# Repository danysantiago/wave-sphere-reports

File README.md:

wave-sphere-reports
===================

Latex reports for the class ICOM5217 - Microprocessor Interfacing and the WaveSphere project.

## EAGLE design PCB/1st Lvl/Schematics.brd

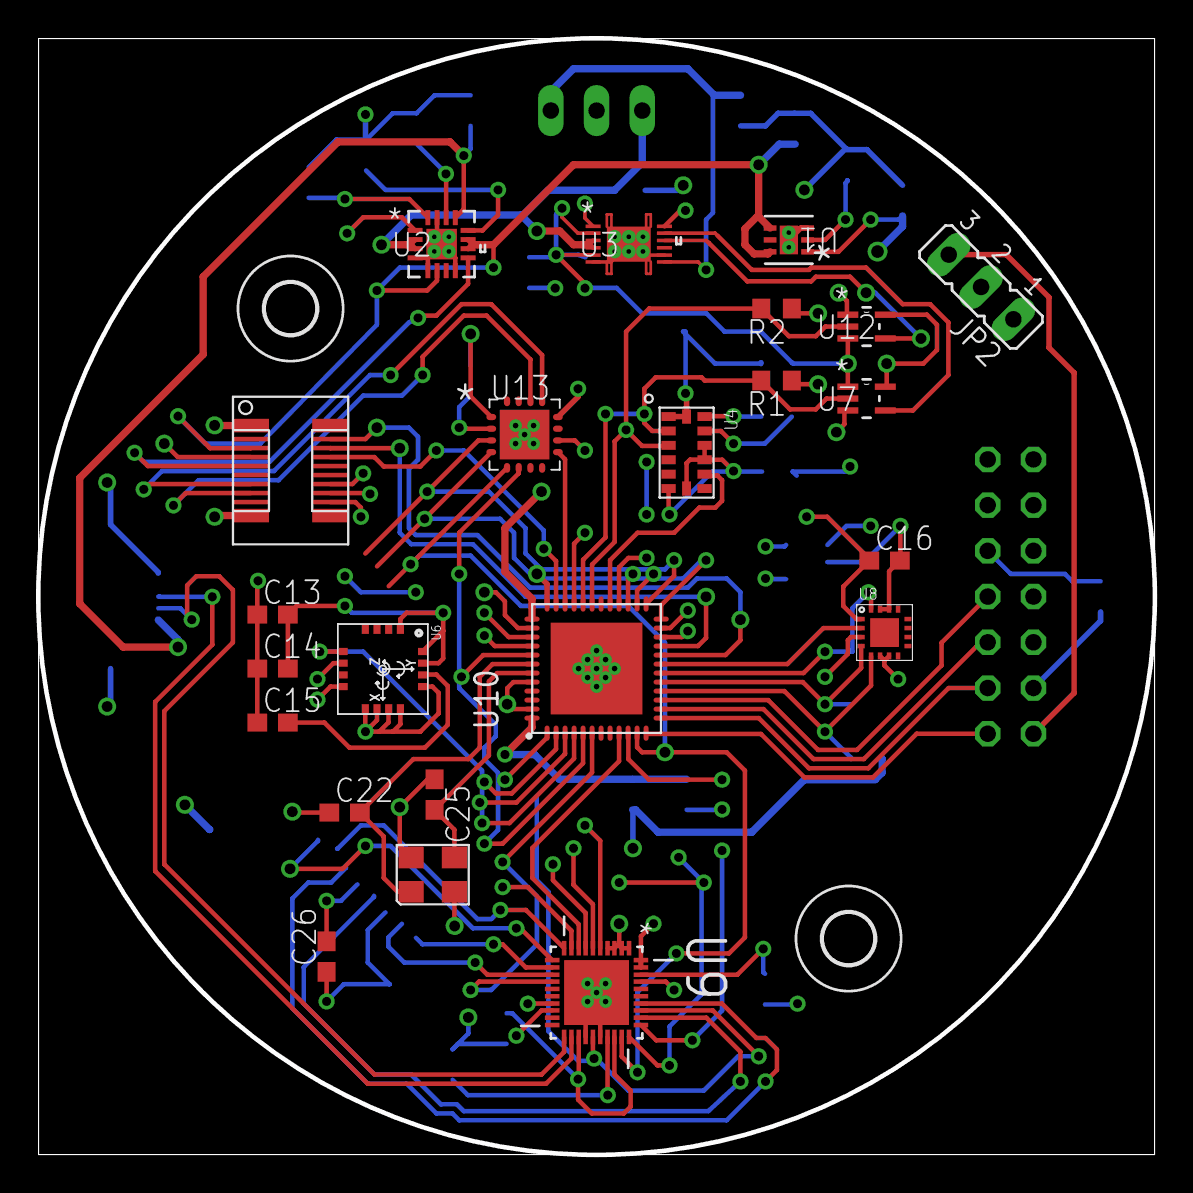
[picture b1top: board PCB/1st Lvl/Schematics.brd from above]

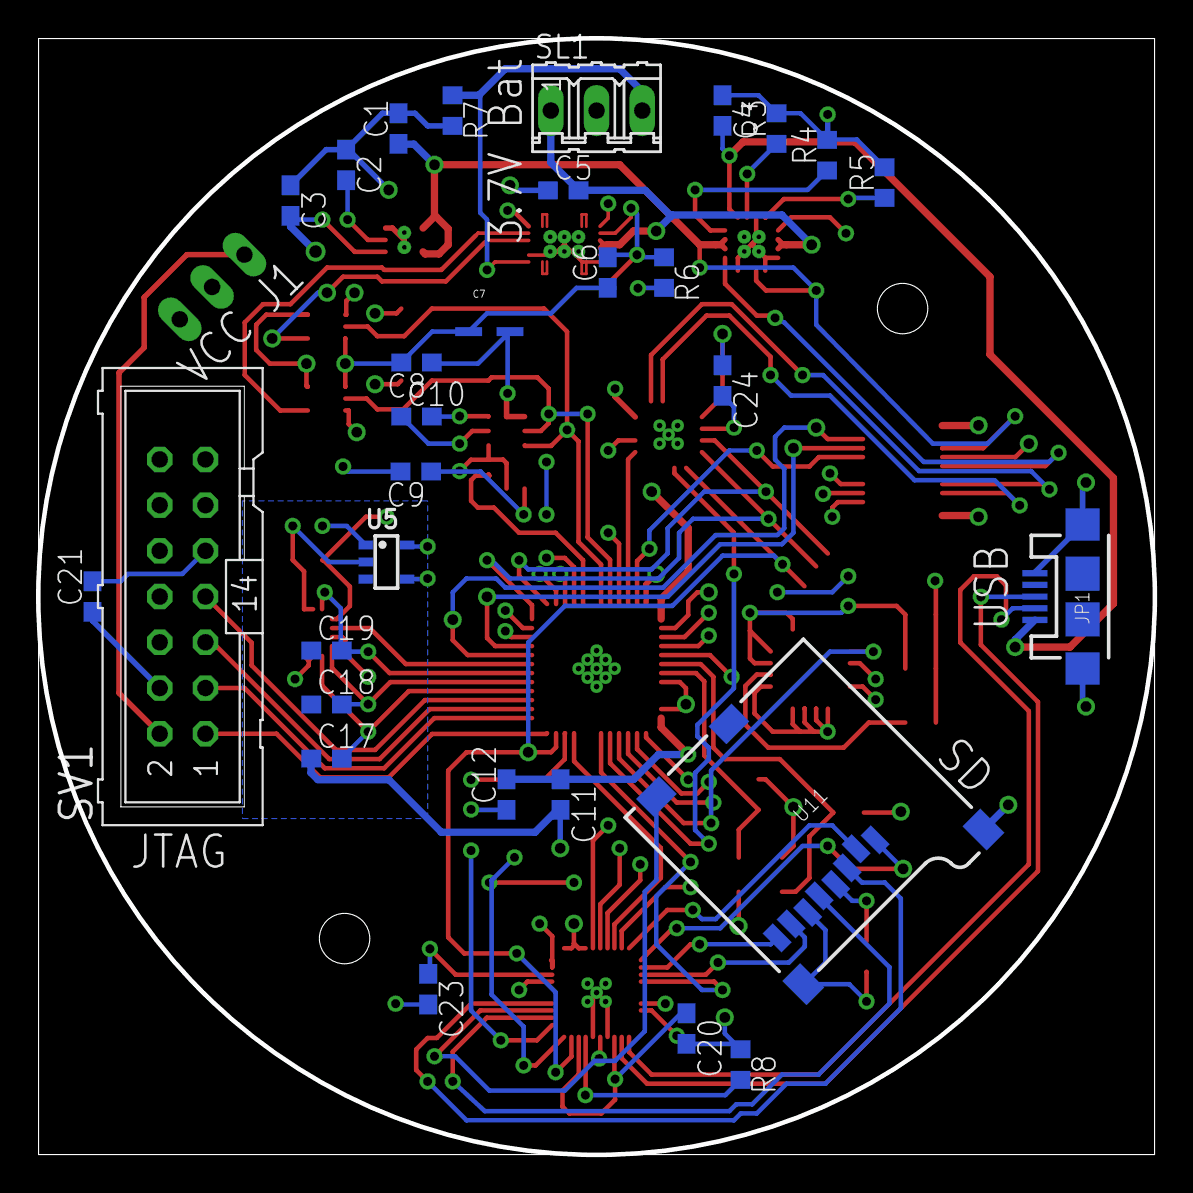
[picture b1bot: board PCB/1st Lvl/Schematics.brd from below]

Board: 4 copper layers, 62.0 x 62.0 mm, 55 parts (30 on the bottom side), 72 nets.

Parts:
C1, C5, C9: 4.7u; C0603
C2, C17, C18, C19: 0.01u; C0603
C3: 2.2u; C0603
C4, C11, C12, C20, C23, C26: 1u; C0603
C6, C8, C13, C14, C16, C24: 0.1u; C0603
C7: 10u; ELECTROLYTIC_CAP
C10: 0.22u; C0603
C15: 1n; C0603
C21: 2.2n; C0603
C22, C25: 22p; C0603
JP1: USB-MICROB
JP2: JP2
JP3: 20-SOCKET
R1, R2: 10k; R0603
R3: 18.7k; R0603
R4: 1.5k; R0603
R5: 1.8k; R0603
R6: 1.8M; R0603
R7: 10m; R0603
R8: 6.19k; R0603
SL1: 3.7V; 03P
SV1: ML14
U1: TPS73533; DRV6_1P6X1
U2: BQ24072_RGT_16; RGT16_1P7X1P7
U3: BQ27410-G1_DRZ_12; DRZ12_1P95X2P45
U4: LSM303DLHC; LGA_3X5X1_14L
U5: BU4S66G2; SSOP5
U6: L3GD20
U7, U12: SN74CB3T1G125_DCK_5; DCK5
U8: ADXL377; LFCSP-16
U9: MAX14502AETL+; QFN40P500X500X80-41N
U10: MSP430FR5969V2; RGZ(S-PVQFN-N48)
U11: SPARKFUN_USD-SOCKETSMD; SPARKFUN_MICRO-SD-SOCKET-PP
U13: AS3930
U$2, U$4: 2,8
X1: 12MHZ

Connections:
AGND: C11.2, C16.1, C17.1, C18.1, C19.1, U5.3, U8.1, U8.3, U8.6, U8.7, U10.41, U10.44, U10.47
BAT_SOC: U3.12, U10.10
CHRG_VCC: C1.1, JP3.3, U1.4, U1.6, U2.6, U2.10, U2.11
D+: JP1.D+, U9.22
D-: JP1.D-, U9.21
GND: C1.2, C2.1, C3.1, C4.1, C5.1, C6.1, C7.-, C8.2, C9.2, C12.1, C13.1, C14.1, C15.1, C20.2, C21.2, C22.1, C23.2, C24.1, C25.1, C26.1, JP1.GND, JP1.MT1, JP1.MT2, JP3.10, R3.2, R4.2, R5.2, R7.2, R8.1, SV1.9, U1.3, U1.7, U1.V, U1.V_2, U2.4, U2.5, U2.8, U2.15, U2.17, U2.V, U2.V_2, U2.V_3, U2.V_4, U3.6, U3.8, U3.13, U3.V, U3.V_2, U3.V_3, U3.V_4, U3.V_5, U3.V_6, U4.P7, U4.P10, U4.P11, U6.4, U6.8, U6.9, U6.10, U6.11, U6.12, U6.13, U7.1, U7.3, U9.1, U9.2, U9.3, U9.4, U9.18, U9.24, U9.26, U9.37, U9.41, U10.36, U10.VSS_QFN, U11.6, U11.GND1, U11.GND2, U12.1, U12.3, U13.7, U13.16, U13.EXP, X1.P$2, X1.P$4
GPS_FIX: JP3.12, U10.3
GYR_DR: U6.6, U10.28
I2CCLK: R1.2, U4.P2, U6.2, U7.2, U10.32
I2CDAT: R2.2, U4.P3, U6.3, U10.31, U12.2
LED1: JP3.5, U2.9
MAG_DR: U4.P9, U10.29
MCU_LED: JP3.4, U10.38
unnamed: U5.5, U10.33
unnamed: C16.2, U5.2, U8.14, U8.15
unnamed: SL1.2, U2.1
unnamed: U3.11, U7.4
unnamed: U8.2, U10.19
unnamed: U3.10, U12.4
unnamed: C15.2, U6.14
unnamed: SV1.1, U10.12
unnamed: C11.1, C12.2, JP2.2, U10.37, U10.48
unnamed: SV1.3, U10.13
unnamed: C22.2, U10.42, X1.P$1
unnamed: C25.2, U10.43, X1.P$3
unnamed: U9.10, U11.2
unnamed: U9.11, U11.1
unnamed: C17.2, U8.5, U10.16
unnamed: U9.12, U11.8
unnamed: C18.2, U8.4, U10.17
unnamed: C19.2, U8.16, U10.18
unnamed: R6.2, U3.1
unnamed: U9.13, U11.7
unnamed: C9.1, U4.P6
unnamed: C10.1, U4.P12
unnamed: C10.2, U4.P13
unnamed: R5.1, U2.16
unnamed: R4.1, U2.12
unnamed: R3.1, U2.14
unnamed: C2.2, U1.2
unnamed: U9.34, U11.3
unnamed: R7.1, SL1.3, U3.7
unnamed: SV1.5, U10.14
unnamed: U9.32, U11.5
unnamed: SV1.7, U10.15
unnamed: C5.2, SL1.1, U2.2, U2.3, U3.3, U3.4
unnamed: U9.33, U11.CD2
unnamed: SV1.8, U10.22
unnamed: R8.2, U9.27
unnamed: C23.1, U9.38
RFWK_CS: U10.5, U13.11
RF_LFN: JP3.7, U13.4
RF_LFP: JP3.8, U13.3
RF_WK: U10.34, U13.8
SD_CD: U9.30, U10.26
SD_CS: U9.14, U10.6
SPI_CLK: U9.29, U10.11, U13.12
SPI_MISO: U9.17, U10.25, U13.14
SPI_MOSI: U9.31, U10.24, U13.13
SU_BERR: U9.6, U10.40
SU_BUSY: U9.7, U10.39
SU_FREF: U9.25, U10.27
SU_MODE: U9.8, U10.9
SWUARTRX: JP3.13, U10.2
SWUARTTX: JP3.14, U10.1
UARTRX: JP3.18, U10.21
UARTTX: JP3.19, U10.20
V2.5: C6.2, R6.1, U3.2, U3.5, U7.5, U12.5
VBUS: C4.2, JP1.VBUS, U2.13
VCC: C3.2, C7.+, C8.1, C13.2, C14.2, C20.1, C21.1, C24.2, C26.2, JP2.1, JP3.1, R1.1, R2.1, SV1.4, SV1.11, U1.1, U4.P1, U4.P14, U5.1, U5.4, U6.1, U6.5, U6.15, U6.16, U9.5, U9.9, U9.23, U9.28, U9.39, U9.40, U10.23, U11.4, U13.5, U13.15
VCC_JTAG: JP2.3, SV1.2
XB_SLEEP: JP3.17, U10.35

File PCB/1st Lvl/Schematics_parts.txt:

Part	Value	Package	Library	Position	Layer

C1  	4.7u  	C0603  	rcl 	  1654   2244	16
C2  	0.01u  	C0603  	rcl 	  1768   2165	16
C3  	2.2u  	C0603  	rcl 	  1890   2087	16
C4  	1u  	C0603  	rcl 	   945   2283	16
C5  	4.7u  	C0603  	rcl 	  1293   2109	16
C6  	0.1u  	C0603  	rcl 	  1196   1929	16
C7  	10u  	ELECTROLYTIC_CAP  	Micro2 	  1455   1800	16
C8  	0.1u  	C0603  	rcl 	  1614   1732	16
C9  	4.7u  	C0603  	rcl 	  1616   1494	16
C10  	0.22u  	C0603  	rcl 	  1614   1614	16
C11  	1u  	C0603  	rcl 	  1299    787	16
C12  	1u  	C0603  	rcl 	  1417    787	16
C13  	0.1u  	C0603  	rcl 	   512   1181	1
C14  	0.1u  	C0603  	rcl 	   512   1063	1
C15  	1n  	C0603  	rcl 	   512    945	1
C16  	0.1u  	C0603  	rcl 	  1850   1299	1
C17  	0.01u  	C0603  	rcl 	  1811    866	16
C18  	0.01u  	C0603  	rcl 	  1811    984	16
C19  	0.01u  	C0603  	rcl 	  1811   1102	16
C20  	1u  	C0603  	rcl 	  1024    276	16
C21  	2.2n  	C0603  	rcl 	  2323   1220	16
C22  	22p  	C0603  	rcl 	   669    748	1
C23  	1u  	C0603  	rcl 	  1589    362	16
C24  	0.1u  	C0603  	rcl 	   945   1693	16
C25  	22p  	C0603  	rcl 	   866    787	1
C26  	1u  	C0603  	rcl 	   630    433	1
JP1  	USB-MICROB  	USB-MICROB  	SparkFun-Connectors 	   157   1220	16
JP2  	  	JP2  	jumper 	  2061   1898	1
JP3  	20-SOCKET  	20-SOCKET  	Micro2 	   551   1496	1
R1  	1.8k  	R0603  	rcl 	  1614   1693	1
R2  	1.8k  	R0603  	rcl 	  1614   1850	1
R3  	18.7k  	R0603  	rcl 	   827   2244	16
R4  	1.5k  	R0603  	rcl 	   716   2186	16
R6  	1.8k  	R0603  	rcl 	   591   2126	16
R7  	1.8M  	R0603  	rcl 	  1073   1929	16
R12  	10m  	R0603  	rcl 	  1535   2283	16
R15  	6.19k  	R0603  	rcl 	   906    197	16
SL1  	3.7V  	03P  	con-amp-quick 	  1220   2283	16
SV1  	  	ML14  	con-ml 	  2126   1220	16
U$2  	  	2,8  	holes 	   551   1850	1
U$4  	  	2,8  	holes 	  1772    472	1
U1  	TPS73533  	DRV6_1P6X1  	Micro2 	  1641   2001	1
U2  	BQ24072_RGT_16  	RGT16_1P7X1P7  	Micro2 	   881   1991	1
U3  	BQ27410-G1_DRZ_12  	DRZ12_1P95X2P45  	Micro2 	  1291   1991	1
U4  	LSM303DLHC  	LGA_3X5X1_14L  	Micro2 	  1417   1535	1
U5  	BU4S66G2  	SSOP5  	Micro2 	  1680   1296	16
U6  	L3GD20  	L3GD20  	Micro2 	   753   1062	1
U7  	SN74CB3T1G125_DCK_5  	DCK5  	Micro2 	  1811   1654	1
U8  	ADXL377  	LFCSP-16  	Micro2 	  1850   1142	1
U9  	MAX14502AETL+  	QFN40P500X500X80-41N  	Micro2 	  1220    354	1
U10  	MSP430FR5969V2  	RGZ(S-PVQFN-N48)  	Micro2 	  1220   1063	1
U11  	SPARKFUN_USD-SOCKETSMD  	SPARKFUN_MICRO-SD-SOCKET-PP  	Micro2 	  1158    737	16
U12  	SN74CB3T1G125_DCK_5  	DCK5  	Micro2 	  1811   1811	1
U13  	AS3930  	AS3930  	Micro2 	  1063   1575	1
X1  	12MHZ  	12MHZ  	12Mhz 	   787    551	1

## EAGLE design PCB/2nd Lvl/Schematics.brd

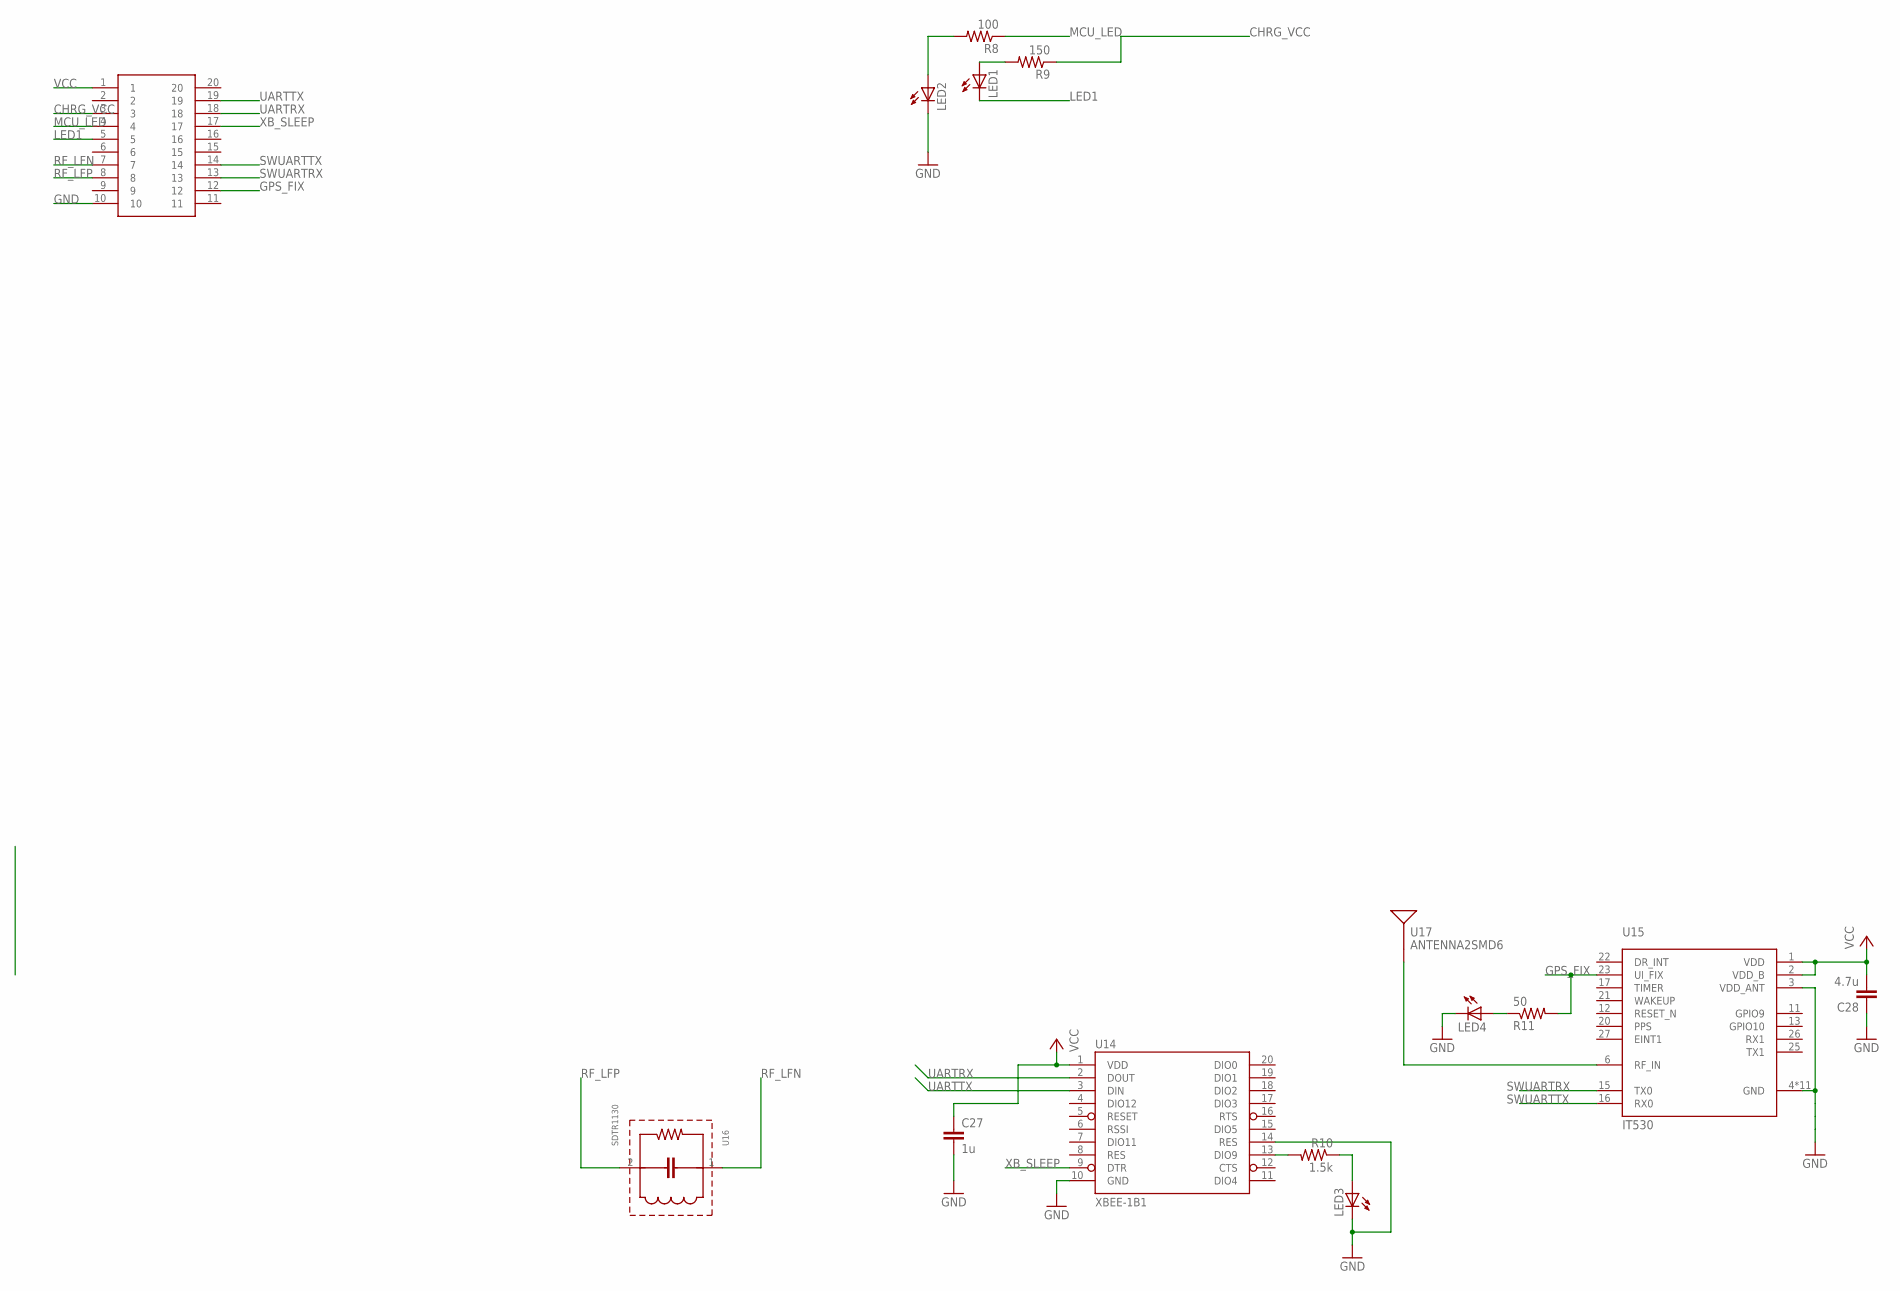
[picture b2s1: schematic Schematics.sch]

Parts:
C27: 1u; C0603
C28: 4.7u; C0603
JP4: 20-HEAD
LED1, LED2, LED3, LED4: LED; SMARTLED-TTW
R8: 100; R0603
R9: 150; R0603
R10: 1.5k; R0603
R11: 50; R0603
U14: XBEE-1B1; XBEE-1
U15: IT530
U16: SDTR1130; SDTR1130-SMD
U17: ANTENNA2SMD6; ANTENNA-CHIP6

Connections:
CHRG_VCC: JP4.3, R9.1
GND: C27.2, C28.1, JP4.10, LED2.C@1 (C), LED3.C@1 (C), LED4.C@1 (C), U14.10 (GND), U14.14 (RES), U15.3 (VDD_ANT), U15.4 (GND), U15.5 (GND), U15.7 (GND), U15.8 (GND), U15.9 (GND), U15.10 (GND), U15.14 (GND), U15.18 (GND), U15.19 (GND), U15.24 (GND), U15.28 (GND)
GPS_FIX: JP4.12, R11.2, U15.23 (UI_FIX)
LED1: JP4.5, LED1.C@1 (C)
MCU_LED: JP4.4, R8.1
unnamed: LED4.A@1 (A), R11.1
unnamed: LED3.A@1 (A), R10.1
unnamed: R10.2, U14.13 (DIO9)
unnamed: U15.6 (RF_IN), U17.1
unnamed: LED1.A@1 (A), R9.2
unnamed: LED2.A@1 (A), R8.2
RF_LFN: JP4.7, U16.1
RF_LFP: JP4.8, U16.2
SWUARTRX: JP4.13, U15.15 (TX0)
SWUARTTX: JP4.14, U15.16 (RX0)
UARTRX: JP4.18, U14.2 (DOUT)
UARTTX: JP4.19, U14.3 (DIN)
VCC: C27.1, C28.2, JP4.1, U14.1 (VDD), U15.1 (VDD), U15.2 (VDD_B)
XB_SLEEP: JP4.17, U14.9 (DTR)

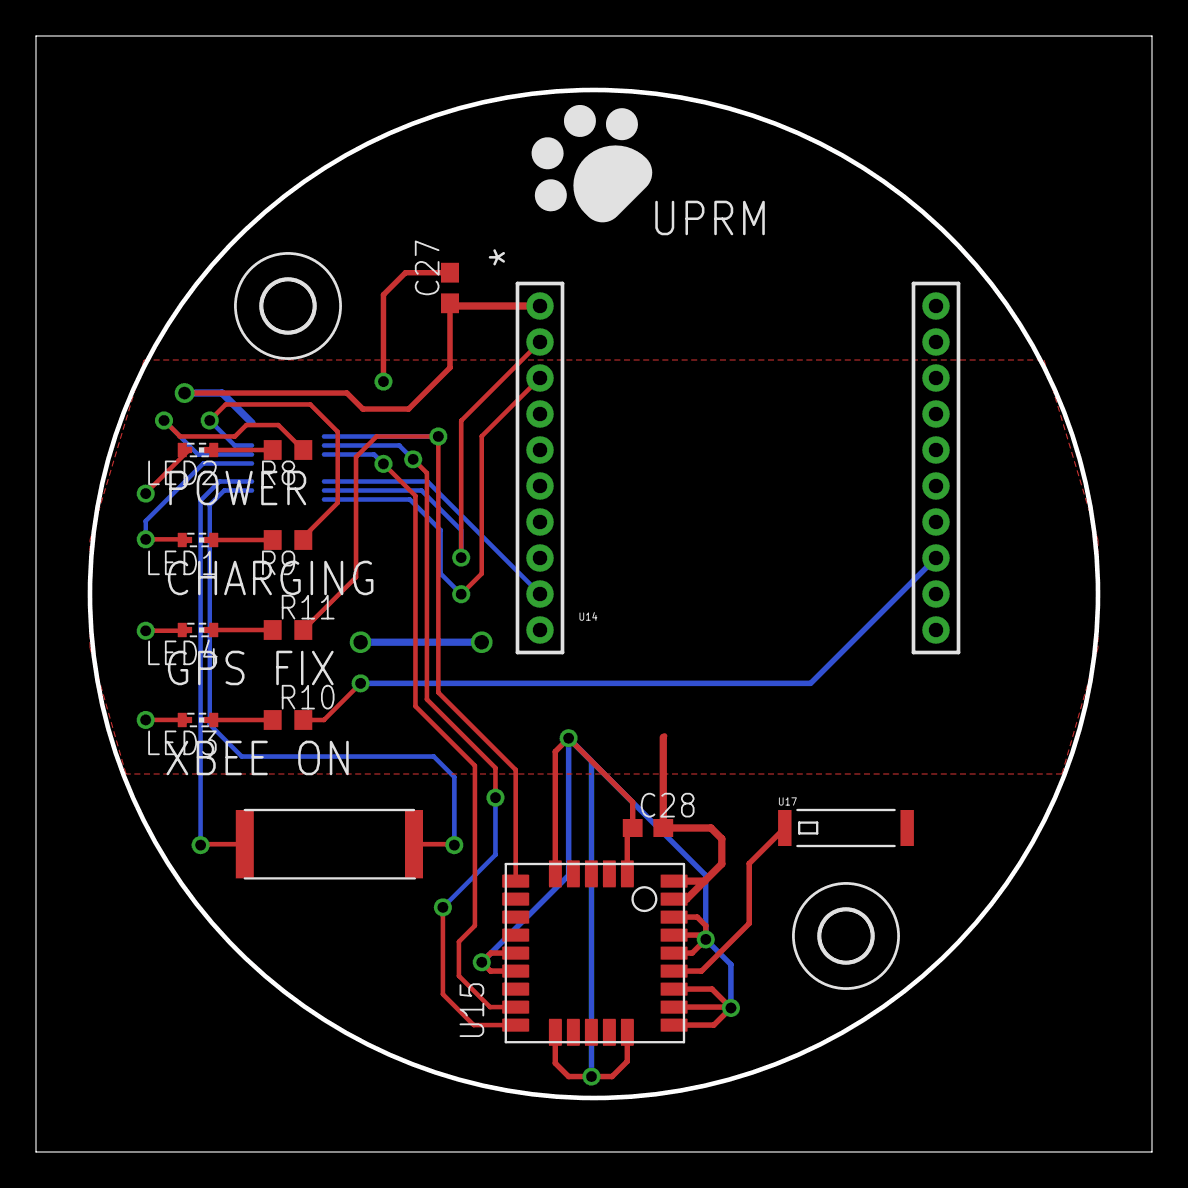
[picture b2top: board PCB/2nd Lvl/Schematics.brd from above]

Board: 2 copper layers, 62.0 x 62.0 mm, 17 parts (1 on the bottom side), 19 nets.

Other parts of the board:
U$4, U$5: 2,8

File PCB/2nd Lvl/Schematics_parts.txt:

EAGLE Version 6.0.0 Copyright (c) 1988-2011 CadSoft
Board partlist for devices with packages for C:/Users/Adrian/Documents/GitHub/wave-sphere-reports/PCB/2nd Lvl/Schematics.sch at 29.04.2013 15:11:53.
The tabulator separated list has been generated with 'Parts v1.3

Part	Value	Package	Library	Position	Layer

C27  	1u  	C0603  	rcl 	   906   1890	1
C28  	4.7u  	C0603  	rcl 	  1339    709	1
JP4  	20-HEAD  	20-HEAD  	Micro2 	   551   1496	16
LED1  	  	SMARTLED-TTW  	led 	   354   1339	1
LED2  	  	SMARTLED-TTW  	led 	   354   1535	1
LED3  	  	SMARTLED-TTW  	led 	   354    945	1
LED4  	  	SMARTLED-TTW  	led 	   354   1142	1
R8  	100  	R0603  	rcl 	   551   1535	1
R9  	150  	R0603  	rcl 	   551   1339	1
R10  	1.5k  	R0603  	rcl 	   551    945	1
R11  	1.5k  	R0603  	rcl 	   551   1142	1
U$4  	  	2,8  	holes 	   551   1850	1
U$5  	  	2,8  	holes 	  1772    472	1
U14  	XBEE-1B1  	XBEE-1  	SparkFun-RF 	  1535   1063	1
U15  	IT530  	IT530  	Micro2 	  1417    630	1
U16  	SDTR1130  	SDTR1130-SMD  	Micro2 	   827    748	1
U17  	ANTENNA2SMD6  	ANTENNA-CHIP6  	SparkFun-RF 	  1772    709	1


= = = = = = = = = = = = = = = = = = = = = = = = = = = = = = = = = = = = = = = = = = = =

Schematic partlist for C:/Users/Adrian/Documents/GitHub/wave-sphere-reports/PCB/2nd Lvl/Schematics.sch

Part	Sheet	Device	Value	Package	Location [inch]

C27  	1	C-EUC0603  	1u  	C0603  	-0.300 -3.900
C28  	1	C-EUC0603  	4.7u  	C0603  	 6.800 -2.900
JP4  	1	20-HEAD  	20-HEAD  	20-HEAD  	-6.500  3.700
LED1  	1	LED  	  	SMARTLED-TTW  	-0.100  4.300
LED2  	1	LED  	  	SMARTLED-TTW  	-0.500  4.200
LED3  	1	LED  	  	SMARTLED-TTW  	 2.800 -4.400
LED4  	1	LED  	  	SMARTLED-TTW  	 3.800 -3.000
R8  	1	R-US_R0603  	100  	R0603  	-0.100  4.600
R9  	1	R-US_R0603  	150  	R0603  	 0.300  4.400
R10  	1	R-US_R0603  	1.5k  	R0603  	 2.500 -4.100
R11  	1	R-US_R0603  	1.5k  	R0603  	 4.200 -3.000
U14  	1	XBEE-1B1  	XBEE-1B1  	XBEE-1  	 1.400 -3.800
U15  	1	IT530  	IT530  	IT530  	 5.500 -3.200
U16  	1	SDTR1130  	SDTR1130  	SDTR1130-SMD  	-2.500 -4.200
U17  	1	ANTENNA2SMD6  	ANTENNA2SMD6  	ANTENNA-CHIP6  	 3.200 -2.400

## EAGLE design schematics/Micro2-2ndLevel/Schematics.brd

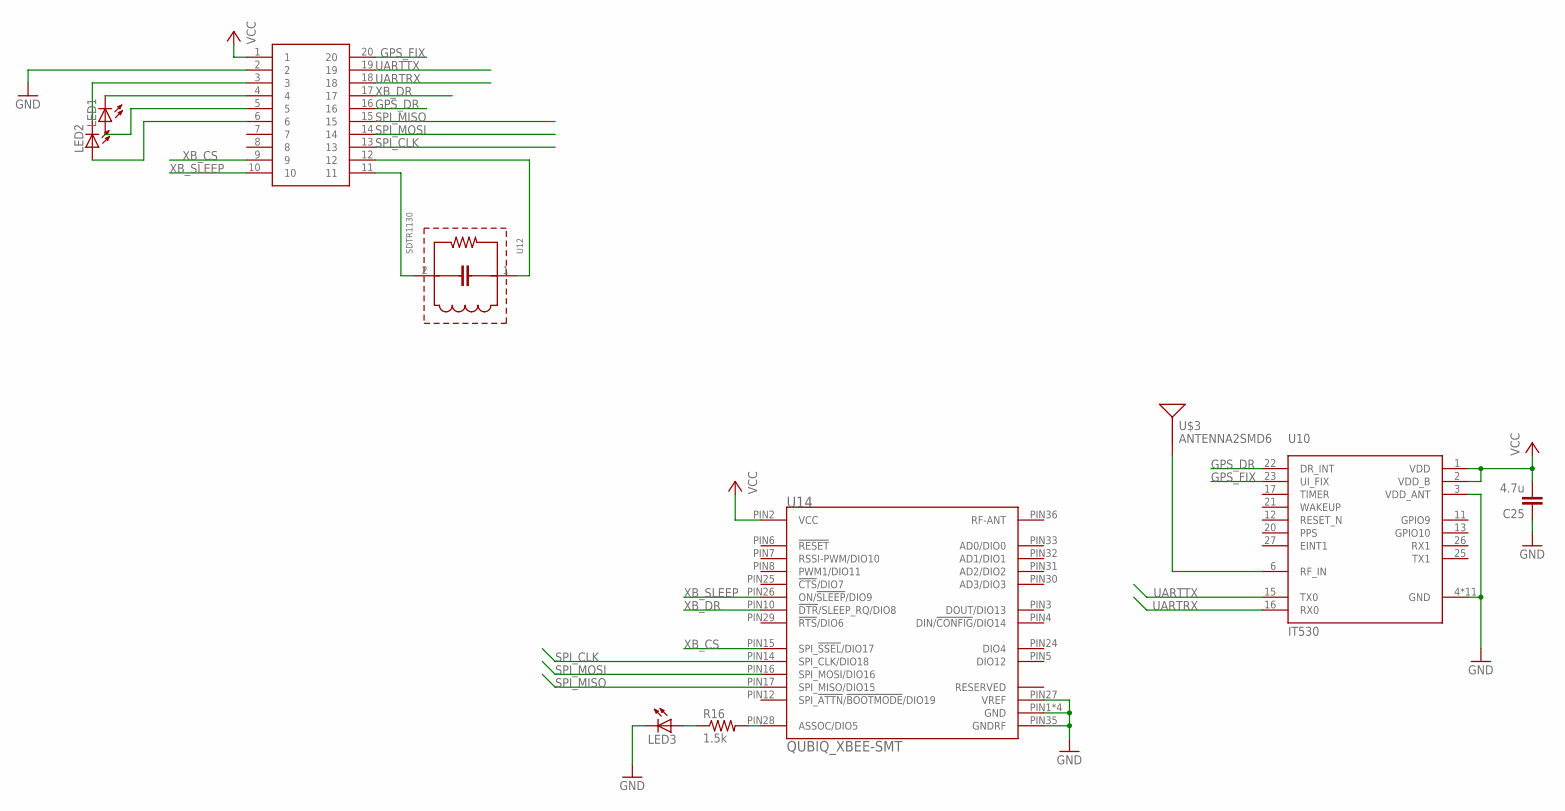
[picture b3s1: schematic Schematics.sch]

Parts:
C25: 4.7u; C0603
LED1, LED2, LED3: LED; SMARTLED-TTW
R16: 1.5k; R0603
U10: IT530
U12: SDTR1130; SDTR1130-SMD
U14: QUBIQ_XBEE-SMT; QUBIQ_FLAT-RF
U$2: 20-HEAD
U$3: ANTENNA2SMD6; ANTENNA-CHIP6

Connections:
GND: C25.1, LED3.C@1 (C), U10.3 (VDD_ANT), U10.4 (GND), U10.5 (GND), U10.7 (GND), U10.8 (GND), U10.9 (GND), U10.10 (GND), U10.14 (GND), U10.18 (GND), U10.19 (GND), U10.24 (GND), U10.28 (GND), U14.PIN1 (GND), U14.PIN11 (GND), U14.PIN13 (GND), U14.PIN22 (GND), U14.PIN27 (VREF), U14.PIN35 (GNDRF), U$2.2
GPS_DR: U10.22 (DR_INT), U$2.16
GPS_FIX: U10.23 (UI_FIX), U$2.20
unnamed: LED2.C@1 (C), U$2.3
unnamed: LED1.C@1 (C), U$2.4
unnamed: LED1.A@1 (A), U$2.5
unnamed: LED2.A@1 (A), U$2.6
unnamed: U12.2, U$2.11
unnamed: U12.1, U$2.12
unnamed: R16.2, U14.PIN28 (ASSOC/DIO5)
unnamed: LED3.A@1 (A), R16.1
unnamed: U10.6 (RF_IN), U$3.1
SPI_CLK: U14.PIN14 (SPI_CLK/DIO18), U$2.13
SPI_MISO: U14.PIN17 (SPI_MISO/DIO15), U$2.15
SPI_MOSI: U14.PIN16 (SPI_MOSI/DIO16), U$2.14
UARTRX: U10.16 (RX0), U$2.18
UARTTX: U10.15 (TX0), U$2.19
VCC: C25.2, U10.1 (VDD), U10.2 (VDD_B), U14.PIN2 (VCC), U$2.1
XB_CS: U14.PIN15 (SPI_!SSEL!/DIO17), U$2.9
XB_DR: U14.PIN10 (!DTR!/SLEEP_RQ/DIO8), U$2.17
XB_SLEEP: U14.PIN26 (ON/!SLEEP!/DIO9), U$2.10

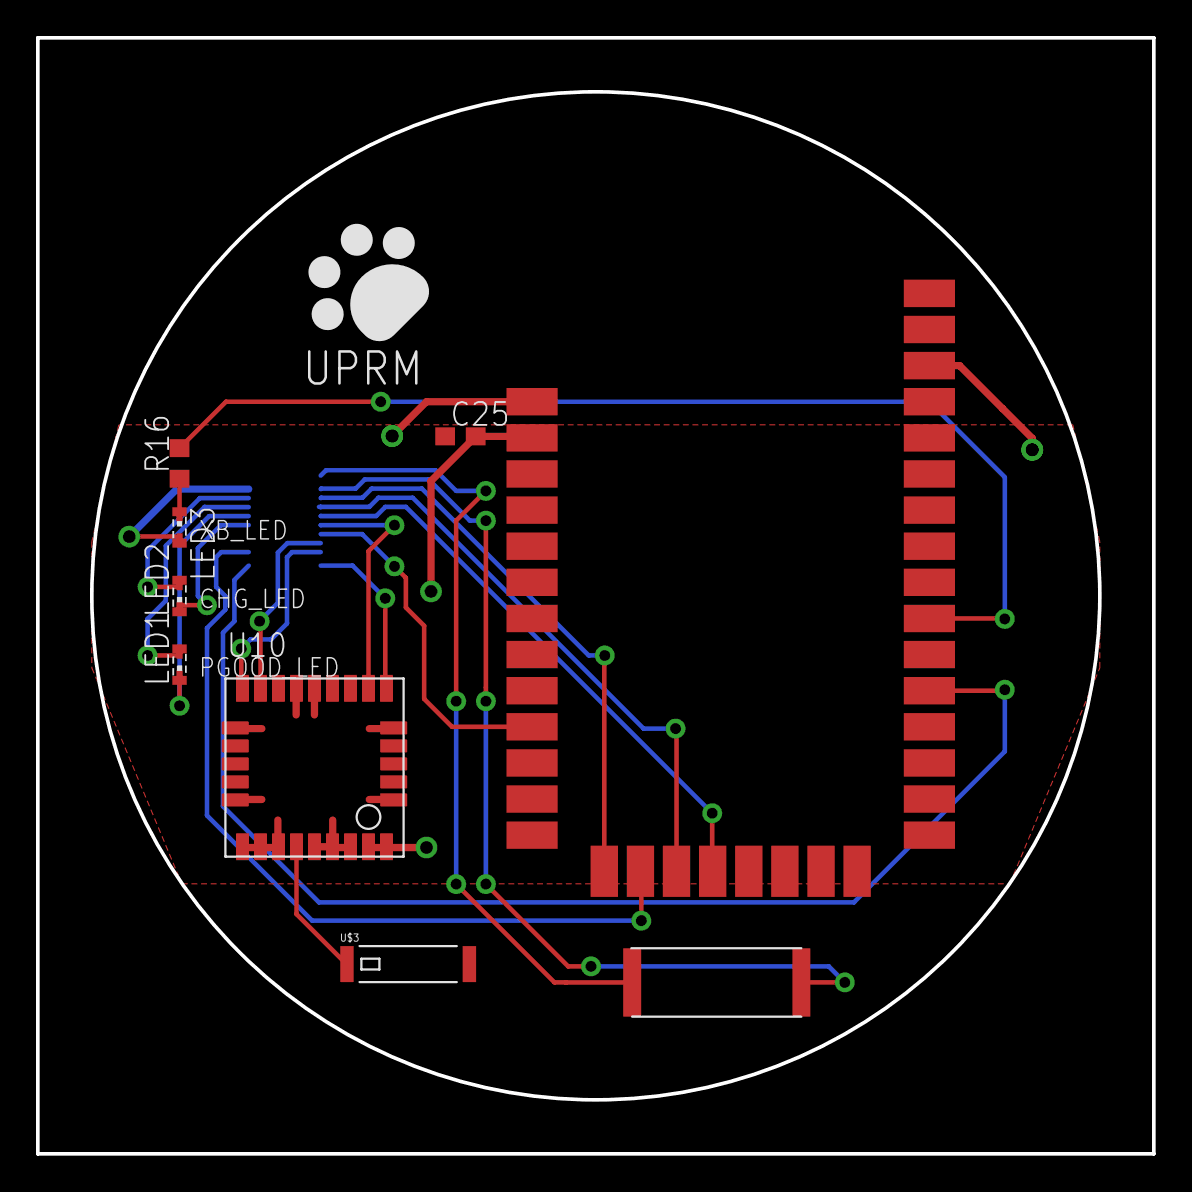
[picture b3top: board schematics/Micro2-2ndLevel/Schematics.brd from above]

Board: 2 copper layers, 62.0 x 62.0 mm, 10 parts (1 on the bottom side), 21 nets.

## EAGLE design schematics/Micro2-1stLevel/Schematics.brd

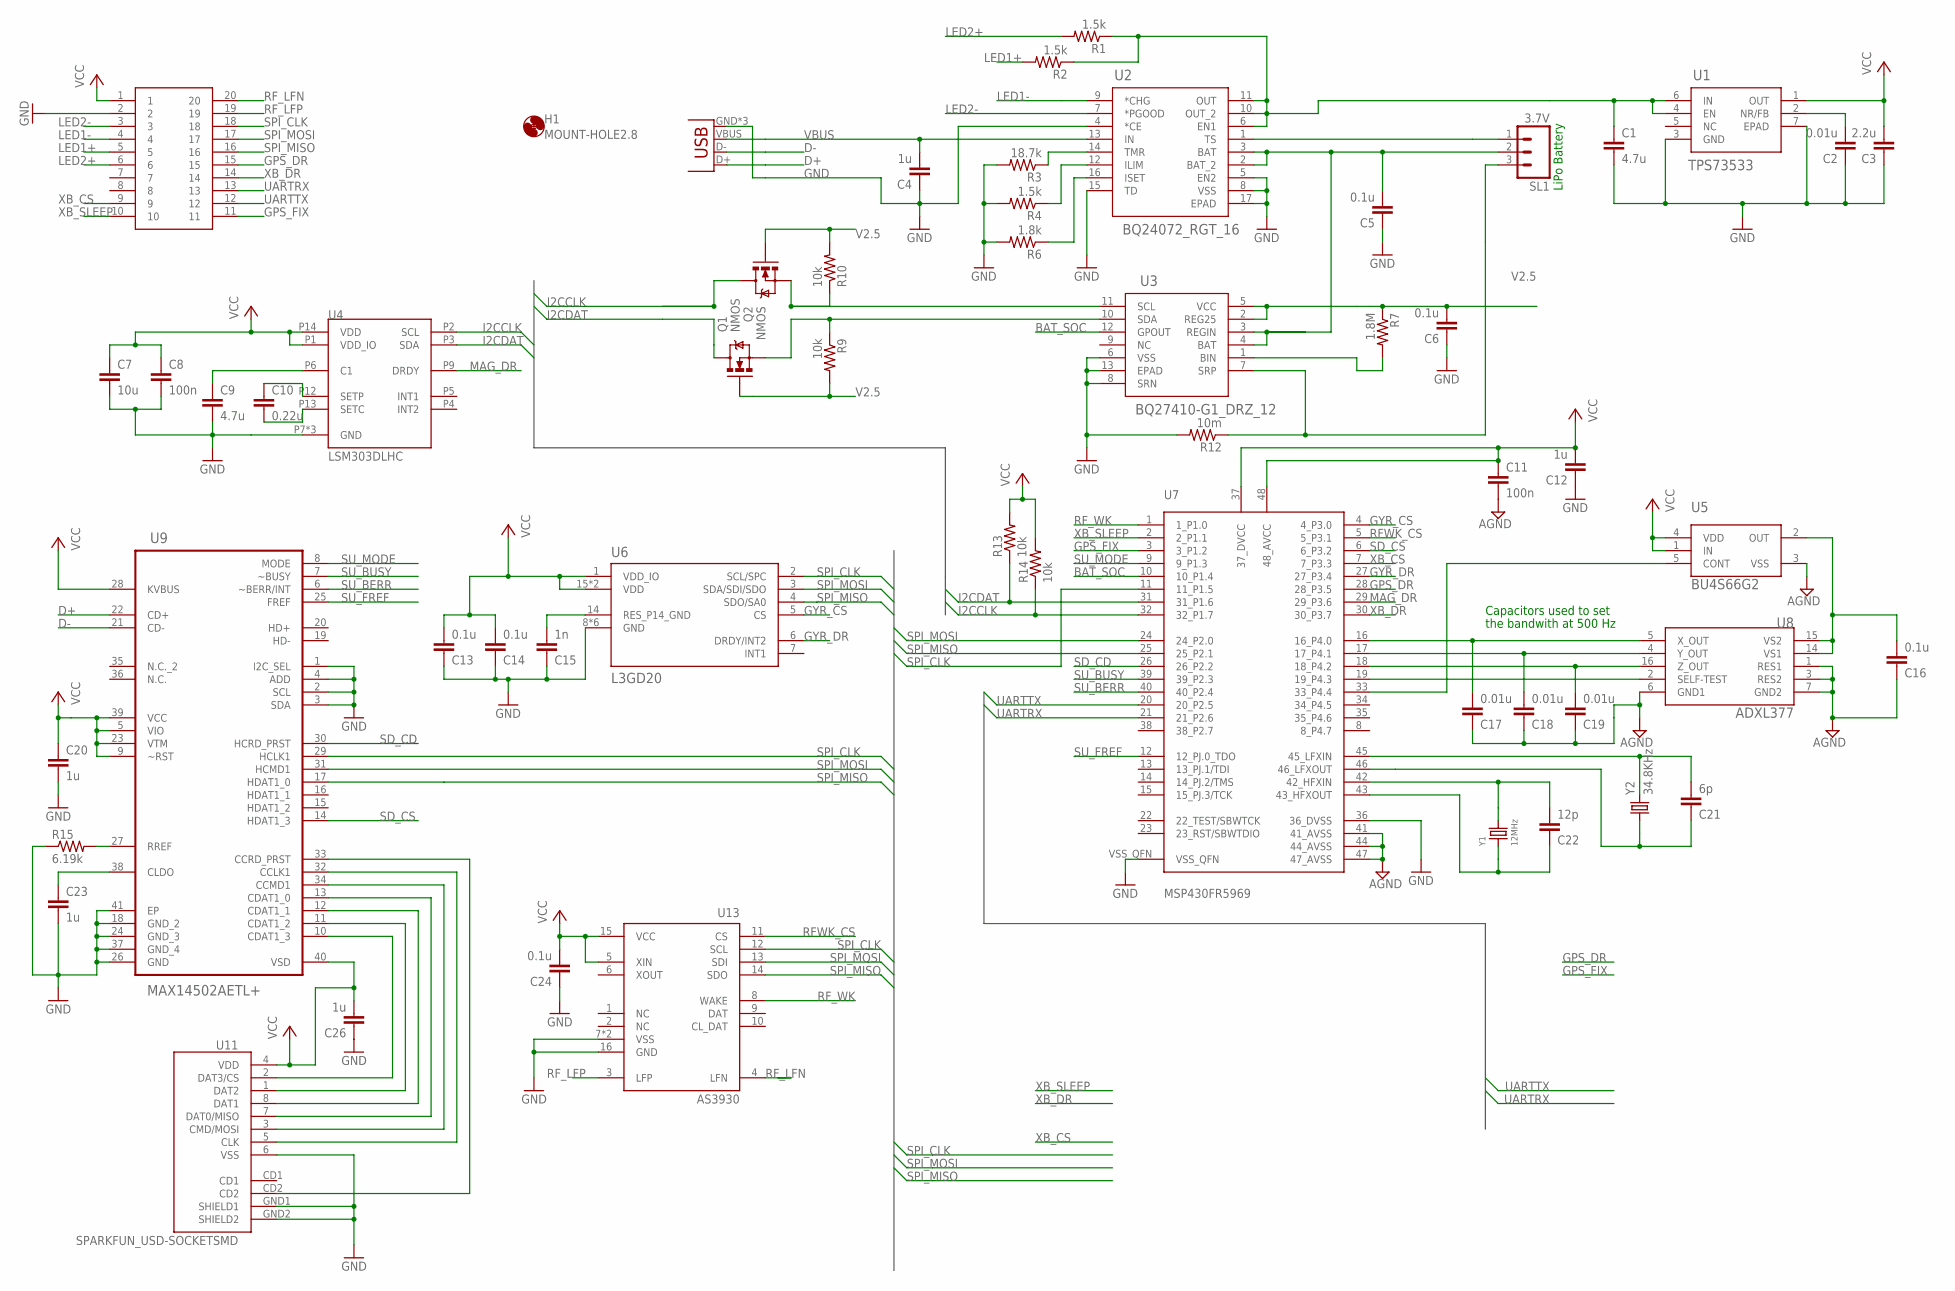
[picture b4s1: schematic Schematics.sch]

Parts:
C1, C9: 4.7u; C0603
C2, C17, C18, C19: 0.01u; C0603
C3: 2.2u; C0603
C4, C12, C20, C23, C26: 1u; C0603
C5, C6, C13, C14, C16, C24: 0.1u; C0603
C7: 10u; C0603
C8, C11: 100n; C0603
C10: 0.22u; C0603
C15: 1n; C0603
C21: 6p; C0603
C22: 12p; C0603
H1: MOUNT-HOLE2.8; 2,8
JP1: USB-MICROB
Q1, Q2: NMOS; SOT23
R1, R2, R4: 1.5k; R0603
R3: 18.7k; R0603
R6: 1.8k; R0603
R7: 1.8M; R0603
R9, R10, R13, R14: 10k; R0603
R12: 10m; R0603
R15: 6.19k; R0603
SL1: 3.7V; 03P
U1: TPS73533; DRV6_1P6X1
U2: BQ24072_RGT_16; RGT16_1P7X1P7
U3: BQ27410-G1_DRZ_12; DRZ12_1P95X2P45
U4: LSM303DLHC; LGA_3X5X1_14L
U5: BU4S66G2; SSOP5
U6: L3GD20
U7: MSP430FR5969; RGZ(S-PQFP-N48)
U8: ADXL377; LFCSP-16
U9: MAX14502AETL+; QFN40P500X500X80-41N
U11: SPARKFUN_USD-SOCKETSMD; SPARKFUN_MICRO-SD-SOCKET-PP
U13: AS3930
U$1: 20-SOCKET
Y1: 12MHz; 3.2X2.5MM
Y2: 34.8KHz; TC38H

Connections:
AGND: C11.2, C16.1, C17.1, C18.1, C19.1, U5.3 (VSS), U7.41 (41_AVSS), U7.44 (44_AVSS), U7.47 (47_AVSS), U8.1 (RES1), U8.3 (RES2), U8.6 (GND1), U8.7 (GND2)
BAT_SOC: U3.12 (GPOUT), U7.10 (10_P1.4)
D+: JP1.D+, U9.22 (CD+)
D-: JP1.D-, U9.21 (CD-)
GND: C1.2, C2.1, C3.1, C4.1, C5.1, C6.1, C7.2, C8.2, C9.2, C12.1, C13.1, C14.1, C15.1, C20.2, C23.2, C24.1, C26.1, JP1.GND, JP1.MT1 (GND), JP1.MT2 (GND), R3.2, R4.2, R6.2, R12.2, R15.1, U1.3 (GND), U1.7 (EPAD), U2.4 (*CE), U2.5 (EN2), U2.8 (VSS), U2.15 (TD), U2.17 (EPAD), U3.6 (VSS), U3.8 (SRN), U3.13 (EPAD), U4.P7 (GND), U4.P10 (GND), U4.P11 (GND), U6.8 (GND), U6.9 (GND), U6.10 (GND), U6.11 (GND), U6.12 (GND), U6.13 (GND), U7.36 (36_DVSS), U7.VSS_QFN, U9.1 (I2C_SEL), U9.2 (SCL), U9.3 (SDA), U9.4 (ADD), U9.18 (GND_2), U9.24 (GND_3), U9.26 (GND), U9.37 (GND_4), U9.41 (EP), U11.6 (VSS), U11.GND1 (SHIELD1), U11.GND2 (SHIELD2), U13.7 (VSS), U13.16 (GND), U13.EXP (VSS), U$1.2
GPS_DR: U7.28 (28_P3.5), U$1.15
GPS_FIX: U7.3 (3_P1.2), U$1.11
GYR_CS: U6.5 (CS), U7.4 (4_P3.0)
GYR_DR: U6.6 (DRDY/INT2), U7.27 (27_P3.4)
I2CCLK: Q2.3 (D), R14.1, U4.P2 (SCL), U7.32 (32_P1.7)
I2CDAT: Q1.3 (D), R13.1, U4.P3 (SDA), U7.31 (31_P1.6)
LED1+: R2.2, U$1.5
LED1-: U2.9 (*CHG), U$1.4
LED2+: R1.2, U$1.6
LED2-: U2.7 (*PGOOD), U$1.3
MAG_DR: U4.P9 (DRDY), U7.29 (29_P3.6)
unnamed: U5.5 (CONT), U7.33 (33_P4.4)
unnamed: C16.2, U5.2 (OUT), U8.14 (VS1), U8.15 (VS2)
unnamed: C21.2, U7.45 (45_LFXIN), Y2.2
unnamed: C21.1, U7.46 (46_LFXOUT), Y2.1
unnamed: U7.19 (19_P4.3), U8.2 (SELF-TEST)
unnamed: Q1.2 (S), R9.1, U3.10 (SDA)
unnamed: C15.2, U6.14 (RES_P14_GND)
unnamed: C22.2, U7.42 (42_HFXIN), Y1.P$3 (2)
unnamed: C1.1, R1.1, R2.1, U1.4 (EN), U1.6 (IN), U2.6 (EN1), U2.10 (OUT_2), U2.11 (OUT)
unnamed: C22.1, U7.43 (43_HFXOUT), Y1.P$1 (1)
unnamed: U9.10 (CDAT1_3), U11.2 (DAT3/CS)
unnamed: U9.11 (CDAT1_2), U11.1 (DAT2)
unnamed: C17.2, U7.16 (16_P4.0), U8.5 (X_OUT)
unnamed: U9.12 (CDAT1_1), U11.8 (DAT1)
unnamed: C18.2, U7.17 (17_P4.1), U8.4 (Y_OUT)
unnamed: C19.2, U7.18 (18_P4.2), U8.16 (Z_OUT)
unnamed: R7.2, U3.1 (BIN)
unnamed: U9.13 (CDAT1_0), U11.7 (DAT0/MISO)
unnamed: Q2.2 (S), R10.1, U3.11 (SCL)
unnamed: C9.1, U4.P6 (C1)
unnamed: C10.1, U4.P12 (SETP)
unnamed: C10.2, U4.P13 (SETC)
unnamed: R6.1, U2.16 (ISET)
unnamed: R4.1, U2.12 (ILIM)
unnamed: R3.1, U2.14 (TMR)
unnamed: C2.2, U1.2 (NR/FB)
unnamed: U9.34 (CCMD1), U11.3 (CMD/MOSI)
unnamed: R12.1, SL1.3, U3.7 (SRP)
unnamed: U9.32 (CCLK1), U11.5 (CLK)
unnamed: C5.2, SL1.2, U2.2 (BAT_2), U2.3 (BAT), U3.3 (REGIN), U3.4 (BAT)
unnamed: SL1.1, U2.1 (TS)
unnamed: U9.33 (CCRD_PRST), U11.CD2
unnamed: R15.2, U9.27 (RREF)
unnamed: C23.1, U9.38 (CLDO)
RFWK_CS: U7.5 (5_P3.1), U13.11 (CS)
RF_LFN: U13.4 (LFN), U$1.20
RF_LFP: U13.3 (LFP), U$1.19
RF_WK: U7.1 (1_P1.0), U13.8 (WAKE)
SD_CD: U7.26 (26_P2.2), U9.30 (HCRD_PRST)
SD_CS: U7.6 (6_P3.2), U9.14 (HDAT1_3)
SPI_CLK: U6.2 (SCL/SPC), U7.11 (11_P1.5), U9.29 (HCLK1), U13.12 (SCL), U$1.18
SPI_MISO: U6.4 (SDO/SA0), U7.25 (25_P2.1), U9.17 (HDAT1_0), U13.14 (SDO), U$1.16
SPI_MOSI: U6.3 (SDA/SDI/SDO), U7.24 (24_P2.0), U9.31 (HCMD1), U13.13 (SDI), U$1.17
SU_BERR: U7.40 (40_P2.4), U9.6 (~BERR/INT)
SU_BUSY: U7.39 (39_P2.3), U9.7 (~BUSY)
SU_FREF: U7.12 (12_PJ.0_TDO), U9.25 (FREF)
SU_MODE: U7.9 (9_P1.3), U9.8 (MODE)
UARTRX: U7.21 (21_P2.6), U$1.13
UARTTX: U7.20 (20_P2.5), U$1.12
V2.5: C6.2, Q1.1 (G), Q2.1 (G), R7.1, R9.2, R10.2, U3.2 (REG25), U3.5 (VCC)
VBUS: C4.2, JP1.VBUS, U2.13 (IN)
VCC: C3.2, C7.1, C8.1, C11.1, C12.2, C13.2, C14.2, C20.1, C24.2, C26.2, R13.2, R14.2, U1.1 (OUT), U4.P1 (VDD_IO), U4.P14 (VDD), U5.1 (IN), U5.4 (VDD), U6.1 (VDD_IO), U6.15 (VDD), U6.16 (VDD), U7.37 (37_DVCC), U7.48 (48_AVCC), U9.5 (VIO), U9.9 (~RST), U9.23 (VTM), U9.28 (KVBUS), U9.39 (VCC), U9.40 (VSD), U11.4 (VDD), U13.5 (XIN), U13.15 (VCC), U$1.1
XB_CS: U7.7 (7_P3.3), U$1.9
XB_DR: U7.30 (30_P3.7), U$1.14
XB_SLEEP: U7.2 (2_P1.1), U$1.10

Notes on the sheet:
Capacitors used to set
the bandwith at 500 Hz
LiPo Battery

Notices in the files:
parts and their libraries:
SparkFun-Connectors: Licensing: CC v3.0 Share-Alike You are welcome to use this library for commercial purposes.
